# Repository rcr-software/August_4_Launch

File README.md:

# Telemetry Test (with possibility for multiprocessing)

On August 4th, 2017, RCR will be performing a test launch of our two stage rocket.  The rcr-software team is using this time to test the design of our new telemetry system as well as hopefully implement some parallel processing using openMP.  The current test plan is to relay values from the RF module on board the rocket to the ground station as fast as possible to develop a clear understanding of the limitations of the telemetry system as well as start developing requirements and redundancies to mitigate chances of data being lost in transmission.

# On-Board Avionics

    Microcomputer/Microcontroller: BeagleBone Black Rev. D
    Operating System: Debian 8.7 2017-03-19 4GB SD IoT (https://debian.beagleboard.org/images/bone-debian-8.7-iot-armhf-2017-03-19-4gb.img.xz)
    Compiler: https://clang.llvm.org/cxx_status.html

    RF Transmitter/Receiver: XBee SX SMD with multidirectional antenna

    Additional Sensors: Adafruit BMP280

# Ground Station

    Microcomputer/Microcontroller: Raspberry Pi 3
    Operating System: Raspbian Jessie

    RF Transmitter/Receiver: XBee SX SMD with multidirectional antenna

# References
- https://jazprojects.wordpress.com/2012/12/23/serial-communication-in-c-in-the-beaglebones-linux-environment-with-an-xbee-example/
- http://elinux.org/ECE497_Project:_XBee
- http://tinkernow.com/2015/01/beaglebone-black-rs232-uart-setup/

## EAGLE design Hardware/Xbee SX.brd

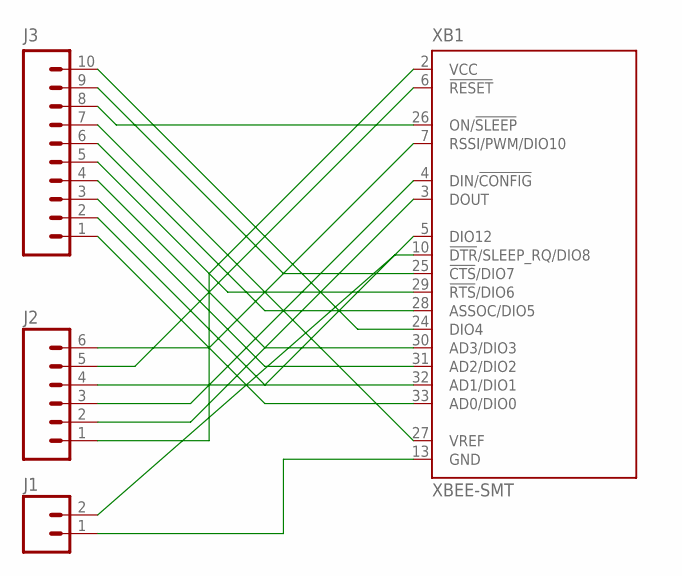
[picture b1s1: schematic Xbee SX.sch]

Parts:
J1: M02PTH; 1X02
J2: M06SILK_FEMALE_PTH; 1X06
J3: M10SILK_FEMALE_PTH; 1X10
XB1: XBEE-SMT

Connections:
GND: J1.1, XB1.13 (GND)
unnamed: J3.10, XB1.24 (DIO4)
unnamed: J3.9, XB1.25 (!CTS!/DIO7)
unnamed: J3.8, XB1.26 (ON/!SLEEP)
unnamed: J3.7, XB1.27 (VREF)
unnamed: J3.6, XB1.28 (ASSOC/DIO5)
unnamed: J3.5, XB1.29 (!RTS!/DIO6)
unnamed: J3.4, XB1.30 (AD3/DIO3)
unnamed: J3.3, XB1.31 (AD2/DIO2)
unnamed: J3.2, XB1.32 (AD1/DIO1)
unnamed: J3.1, XB1.33 (AD0/DIO0)
unnamed: J2.1, XB1.2 (VCC)
unnamed: J2.2, XB1.3 (DOUT)
unnamed: J2.3, XB1.4 (DIN/!CONFIG)
unnamed: J2.4, XB1.5 (DIO12)
unnamed: J2.5, XB1.6 (!RESET)
unnamed: J2.6, XB1.7 (RSSI/PWM/DIO10)
unnamed: J1.2, XB1.10 (!DTR!/SLEEP_RQ/DIO8)

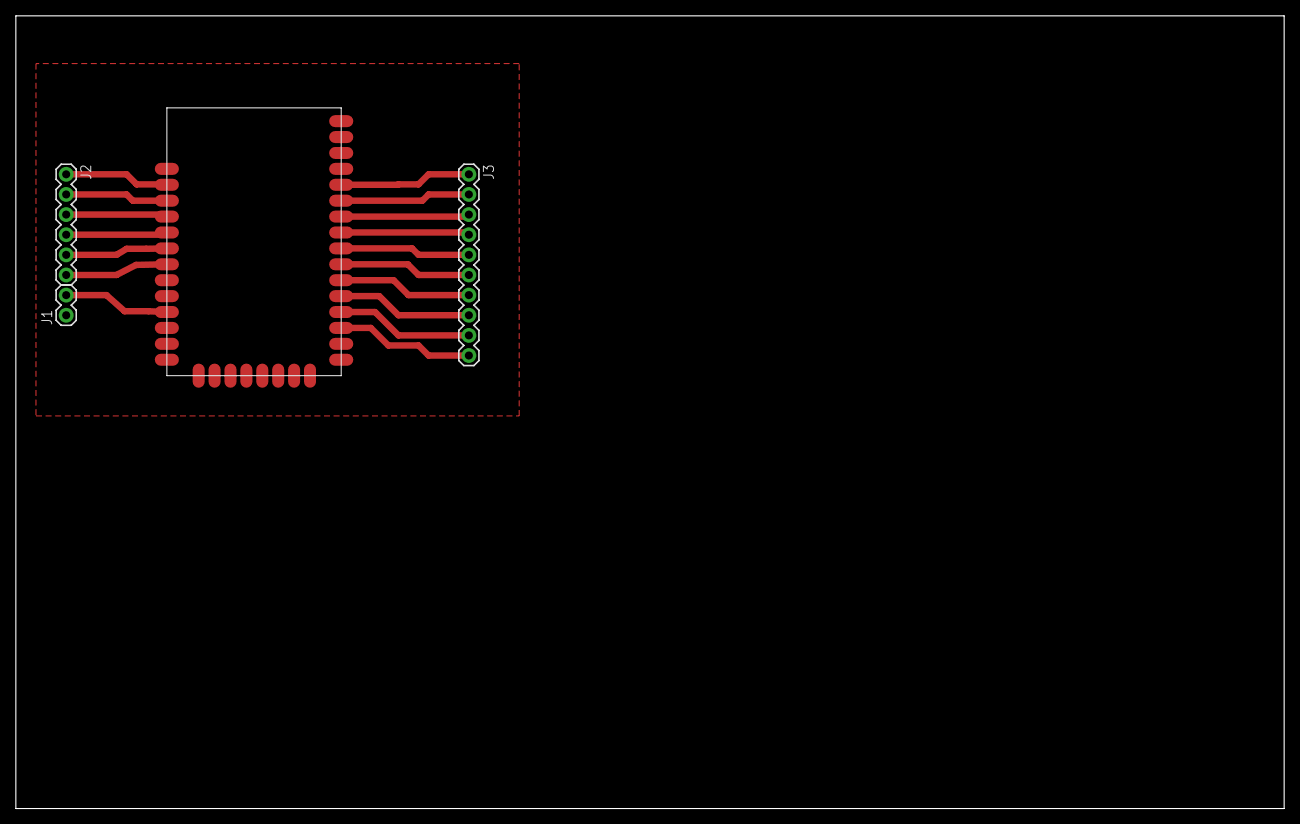
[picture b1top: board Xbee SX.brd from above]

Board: 2 copper layers, 160.0 x 100.0 mm, 4 parts (0 on the bottom side), 18 nets.

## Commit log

2017-07-17 Rename Lib/control.h to Hermes/lib/control.h
2017-07-17 Rename Lib/uart.h to Hermes/lib/uart.h

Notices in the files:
parts and their libraries:
SparkFun-Connectors: Licensing: Creative Commons ShareAlike 4.0 International - https://creativecommons.org/licenses/by-sa/4.0
